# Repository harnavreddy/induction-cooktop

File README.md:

# induction-cooktop
Simulation of an Induction Cooktop Circuit, Implementation of Control and Safety Features for an Induction Cooktop Using Microcontroller Unit
The induction hob is a cutting-edge feature found in modern kitchens. It offers fast and accurate cooking, as well as improved energy efficiency and safety. The demand for induction hob designs that align with evolving culinary practices and prioritize sustainability has grown significantly. These designs aim to not only meet these demands but also enhance the overall cooking experience. The objective of this project is to develop an induction hob that prioritizes efficiency and safety, while also incorporating user-friendly features and a visually appealing design.
The crux of this project involves the identification and resolution of the constraints associated with current induction cooktops. Although these appliances provide notable benefits compared to traditional cooking methods, they frequently have limitations in terms of heat distribution, user interface design, and compatibility with different types of cookware materials. This project aims to address and overcome the challenges associated with induction cooktops, with the goal of revolutionising and redefining their standard. The ultimate objective is to position induction cooktops as leading-edge kitchen appliances in the modern era.
The objective of this project is to conceptualize and develop a hob that demonstrates exceptional performa- nce, versatility, and user satisfaction by thoroughly examining materials, technologies, and user requirements. The design will meticulously craft every aspect, from optimizing the electromagnetic induction system to enhancing safety features like automatic pan detection and child lock mechanisms. This will result in a seamless and enriching cooking experience.
Moreover, this project acknowledges the significance of sustainability in the design and manufacturing of products. The design process of our cooktop prioritizes energy efficiency, recyclability, and longevity. Our goal is to create a cooktop that not only enhances the lives of users but also minimizes its environmental footprint.
This project explores the intricacies of electromagnetic induction, which is the fundamental principle that underlies the operation of induction hobs in the field of electrical engineering. By employing a rigorous approach to optimizing the electromagnetic induction system, which encompasses the meticulous design of the induction coils and control circuitry, our objective is to achieve the highest possible energy transfer efficiency while also guaranteeing accurate control over cooking temperatures. The induction coils will be regulated using advanced power electronics and control algorithms, enabling rapid heating and precise power control on the cooking surface.

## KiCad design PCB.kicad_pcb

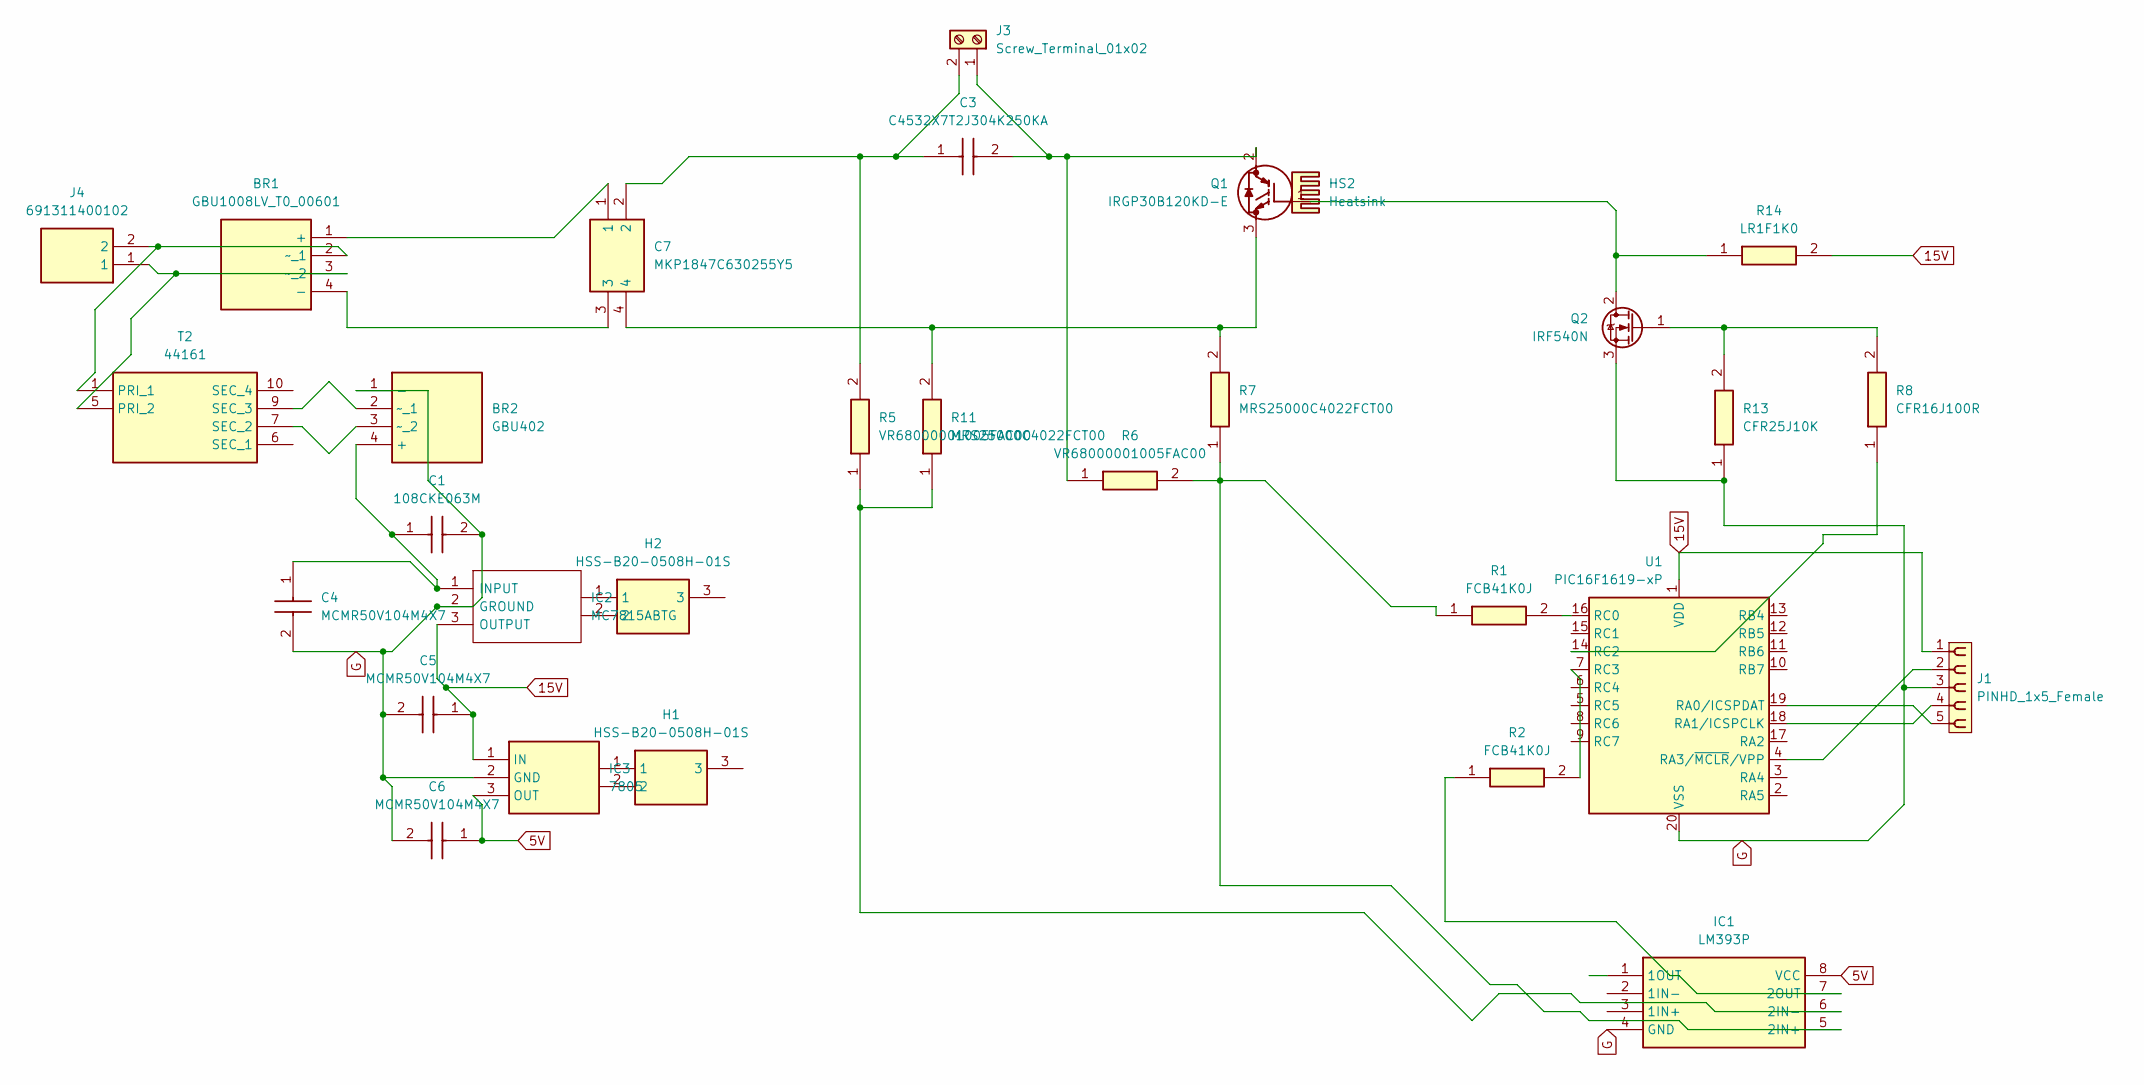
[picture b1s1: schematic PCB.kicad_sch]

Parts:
BR1: GBU1008LV_T0_00601; GBU610; Manufacturer_Part_Number GBU1008LV_T0_00601; Mouser Part Number 241-GBU1008LVT000601
BR2: GBU402; TO508P356X2205X2083-4P; Manufacturer_Part_Number GBU402; Mouser Part Number 821-GBU402
C1: 108CKE063M; CAPPRD750W80D1625H2700; Manufacturer_Part_Number 108CKE063M
C3: C4532X7T2J304K250KA; C4532_Commercial; Manufacturer_Part_Number C4532X7T2J304K250KA; Mouser Part Number 810-C4532X7T2J304K2A
C4, C5, C6: MCMR50V104M4X7; CAPPRD150W50D425H800; Manufacturer_Part_Number MCMR50V104M4X7
C7: MKP1847C630255Y5; Manufacturer_Part_Number MKP1847C630255Y5; Mouser Part Number 75-MKP1847C630255Y5
H1, H2: HSS-B20-0508H-01S; HSSB200508H01S; Manufacturer_Part_Number HSS-B20-0508H-01S; Mouser Part Number 490-HSS-B20-0508H01S
HS2: Heatsink; Heatsink_AAVID_TV5G_TO220_Horizontal
IC1: LM393P; DIP794W53P254L959H508Q8N; Manufacturer_Part_Number LM393P; Mouser Part Number 595-LM393P
IC2: MC7815ABTG; TO254P482X997X2018-3P; Manufacturer_Part_Number MC7815ABTG; Mouser Part Number 863-MC7815ABTG
IC3: 7805; TO254P470X1000X1610-3P; Manufacturer_Part_Number 7805
J1: PINHD_1x5_Female; PinSocket_1x05_P2.54mm_Vertical
J3: Screw_Terminal_01x02; TerminalBlock_Wuerth_691311400102_P7.62mm
J4: 691311400102; Manufacturer_Part_Number 691311400102; Mouser Part Number 710-691311400102
Q1: IRGP30B120KD-E; TO546P513X1558X2499-3P; Manufacturer_Part_Number IRGP30B120KD-E
Q2: IRF540N; TO-220-3_Vertical
R1, R2: FCB41K0J; Manufacturer_Part_Number FCB41K0J; Mouser Part Number 279-FCB41K0J
R5, R6: VR68000001005FAC00; RESAD4520W83L1800D680; Manufacturer_Part_Number VR68000001005FAC00; Mouser Part Number 594-VR68000001005FAC
R7, R11: MRS25000C4022FCT00; RESAD1650W60L650D250; Manufacturer_Part_Number MRS25000C4022FCT00
R8: CFR16J100R; RESAD1090W50L350D185; Manufacturer_Part_Number CFR16J100R; Mouser Part Number 279-CFR16J100R
R13: CFR25J10K; RESAD1680W54L680D250; Manufacturer_Part_Number CFR25J10K; Mouser Part Number 279-CFR25J10K
R14: LR1F1K0; RESAD1540W55L620D230; Manufacturer_Part_Number LR1F1K0; Mouser Part Number 279-LR1F1K0
T2: 44161; Manufacturer_Part_Number 44161
U1: PIC16F1619-xP; DIP-20_W7.62mm

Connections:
5V: C6.1 (+), IC1.8 (VCC), IC3.3 (OUT)
15V: C5.1 (+), IC2.3 (OUTPUT), IC3.1 (IN), J1.1, R14.2, U1.1 (VDD)
G: BR2.1 (-), C1.2 (-), C4.2 (-), C5.2 (-), C6.2 (-), IC1.4 (GND), IC2.2 (GROUND), IC3.2 (GND), J1.3, Q2.3 (S), R13.1, U1.20 (VSS)
unnamed: BR1.1 (+), C7.1
unnamed: BR1.4 (-), C7.3
unnamed: BR1.2 (~_1), J4.2, T2.1 (PRI_1)
unnamed: BR1.3 (~_2), J4.1, T2.5 (PRI_2)
unnamed: BR2.4 (+), C1.1 (+), C4.1 (+), IC2.1 (INPUT)
unnamed: BR2.2 (~_1), T2.9 (SEC_3)
unnamed: BR2.3 (~_2), T2.7 (SEC_2)
unnamed: IC1.5 (2IN+), R1.1, R6.2, R7.1
unnamed: IC1.6 (2IN-), R5.1, R11.1
unnamed: IC1.7 (2OUT), R2.1
unnamed: C3.2, J3.1, Q1.2 (C), R6.1
unnamed: C3.1, C7.2, J3.2, R5.2
unnamed: C7.4, Q1.3 (E), R7.2, R11.2
unnamed: Q1.1 (G), Q2.2 (D), R14.1
unnamed: Q2.1 (G), R8.2, R13.2
unnamed: J1.5, U1.19 (RA0/ICSPDAT)
unnamed: J1.4, U1.18 (RA1/ICSPCLK)
unnamed: J1.2, U1.4 (RA3/~MCLR/VPP)
unnamed: R1.2, U1.16 (RC0)
unnamed: R8.1, U1.14 (RC2)
unnamed: R2.2, U1.7 (RC3)

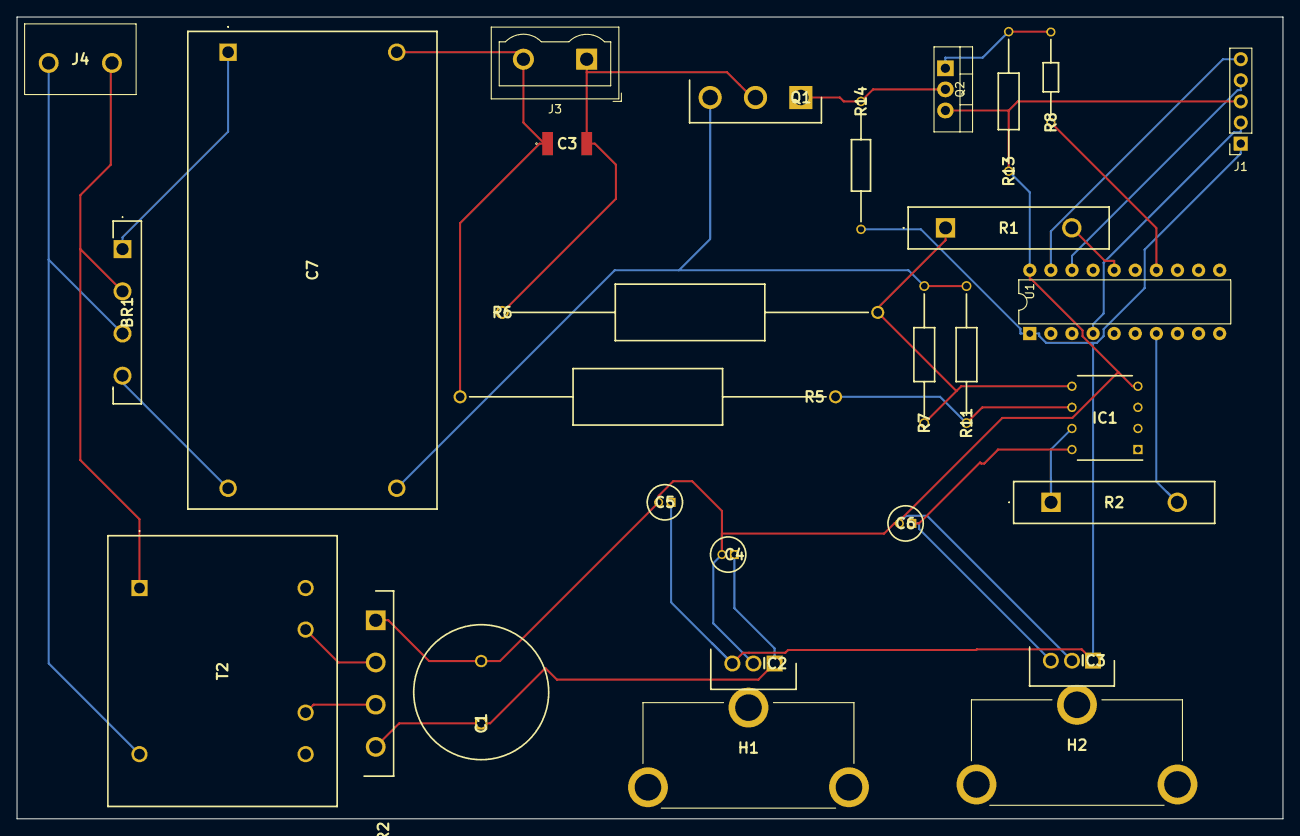
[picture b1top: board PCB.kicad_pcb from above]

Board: 2 copper layers, 152.4 x 96.5 mm, 29 parts (0 on the bottom side), 24 nets.
